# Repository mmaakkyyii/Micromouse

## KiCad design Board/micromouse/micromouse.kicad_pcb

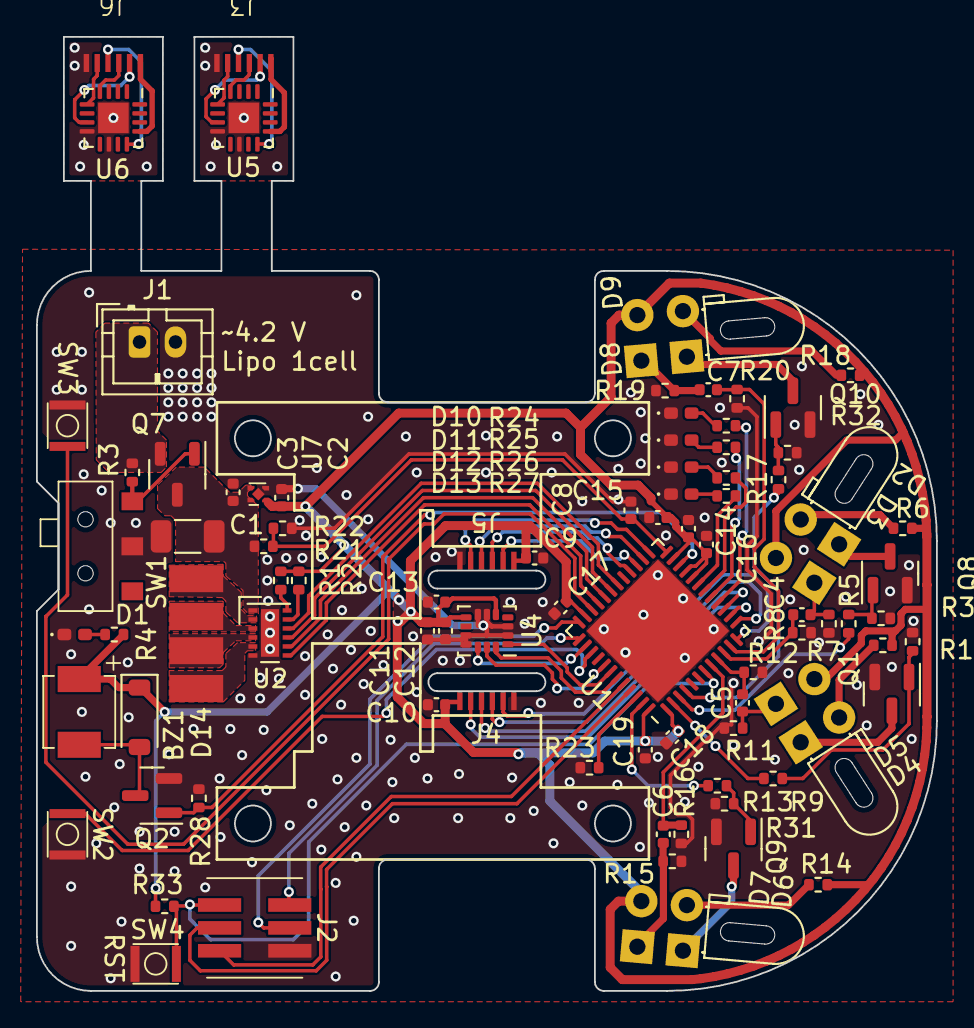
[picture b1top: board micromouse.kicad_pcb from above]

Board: 2 copper layers, 50.0 x 53.0 mm, 91 parts (0 on the bottom side), 83 nets.

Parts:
BZ1: SMT-0440-T-HT-R
C1: 10u; C_1206_3216Metric
C2, C3: 1u; C_0402_1005Metric
C4, C5, C6, C7: 0.01u; C_0402_1005Metric
C8, C9, C10, C12, C14, C15, C16, C17, C18, C19: 0.1u; C_0402_1005Metric
C11: 2.2u; C_0402_1005Metric
C13: 10n; C_0402_1005Metric
D1, D10, D11, D12, D13: LED; LED_0402_1005Metric_Pad0.77x0.64mm_HandSolder
D2, D4, D6, D8: OSI5FU3A11C; LED
D3, D5, D7, D9: LTR-4206E; PhotoDiode
D14: 1N4448W-TP; D_SOD-123
J1: Conn_01x02_Pin; JST_PH_B2B-PH-K_1x02_P2.00mm_Vertical
J2: Conn_02x03_Odd_Even; 20021221-00006C4LF
J3, J4, J5, J6: Conn_01x06_Pin; ENC_CONN
M1, M2: Motor_DC; Motor_PAD
Q1, Q2, Q8, Q9, Q10: DMN63D8L-7; SOT-23
Q7: GSFC02A05; SOT-23-3
R1, R2, R23: 0; R_0402_1005Metric
R3: 100k; R_0402_1005Metric
R4, R24, R25, R26, R27: 3.3k; R_0402_1005Metric
R5, R9, R13, R17: 10; R_0402_1005Metric
R6, R10, R14, R18: 15; R_0402_1005Metric
R7, R11, R15, R19: 300; R_0402_1005Metric
R8, R12, R16, R20, R28, R29, R30, R31, R32, R33: 10k; R_0402_1005Metric
R21: 6.8k; R_0402_1005Metric
R22: 15k; R_0402_1005Metric
SW1: AYZ0102AGRLC
SW2, SW3, SW4: NANOT 100 AS
U1: STM32G474CEUx; QFN-48-1EP_7x7mm_P0.5mm_EP5.6x5.6mm
U2: DRV8836DSSR; WSON-12-1EP_3x2mm_P0.5mm_EP1x2.65
U4: ICM-42688-P; LGA-14_3x2.5mm_P0.5mm_LayoutBorder3x4y
U5, U6: MAQ473GQE-AEC1-Z; QFN-16-1EP_3x3mm_P0.5mm_EP1.7x1.7mm
U7: NCP177AMX330TCG; XDFN4 1.0x1.0, 0.65P

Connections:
+3.3V: BZ1.1 (-), C2.1, C9.1, C10.1, C11.1, C12.1, C13.1, C14.1, C15.1, C16.1, C17.1, C18.1, C19.1, D3.2 (A), D5.2 (A), D7.2 (A), D9.2 (A), D14.1 (K), J4.1, J5.1, R1.2, R2.2, R4.1, R6.1, R10.1, R14.1, R18.1, R33.1, U1.1 (VBAT), U1.20 (VREF+), U1.21 (VDDA), U1.23 (VDD), U1.35 (VDD), U1.48 (VDD), U4.5 (VDDIO), U4.8 (VDD), U7.1 (OUT)
/AIN1: U1.30 (PA8), U2.10 (AIN1/APHASE)
/AIN2: U1.31 (PA9), U2.9 (AIN2/AENBL)
/BATT_ADC: C8.1, R21.2, R22.1, U1.24 (PB11)
/BIN1: U1.32 (PA10), U2.8 (BIN1/BPHASE)
/BIN2: U1.33 (PA11), U2.7 (BIN2/BENBL)
/BUZZER: Q2.1 (G), R28.2, U1.22 (PB10)
/ENC1/ENC_CS: J6.5, U6.5 (CS)
/ENC1/ENC_GND: J6.6, U6.8 (GND), U6.10 (TEST), U6.17 (EX_PAD)
/ENC1/ENC_MISO: J6.2, U6.7 (MISO)
/ENC1/ENC_MOSI: J6.3, U6.4 (MOSI)
/ENC1/ENC_SCLK: J6.4, U6.12 (SCLK)
/ENC1/ENC_VDD: J6.1, U6.13 (VDD)
/ENC/ENC_CS: J3.5, U5.5 (CS)
/ENC/ENC_GND: J3.6, U5.8 (GND), U5.10 (TEST), U5.17 (EX_PAD)
/ENC/ENC_MISO: J3.2, U5.7 (MISO)
/ENC/ENC_MOSI: J3.3, U5.4 (MOSI)
/ENC/ENC_SCLK: J3.4, U5.12 (SCLK)
/ENC/ENC_VDD: J3.1, U5.13 (VDD)
/LED1: R24.2, U1.16 (PC4)
/LED2: R25.2, U1.17 (PB0)
/LED3: R26.2, U1.18 (PB1)
/LED4: R27.2, U1.19 (PB2)
/LED_FL: R17.1, U1.4 (PC15)
/LED_FR: R13.1, U1.47 (PB9)
/LED_L: R5.1, U1.3 (PC14)
/LED_R: R9.1, U1.2 (PC13)
/NRST: J2.1, R33.2, SW4.2, U1.7 (PG10)
/SENSOR_FL: C7.2, R20.1, U1.11 (PA3)
/SENSOR_FR: C6.2, R16.1, U1.8 (PA0)
/SENSOR_L: C4.2, R8.1, U1.10 (PA2)
/SENSOR_R: C5.2, R12.1, U1.9 (PA1)
/SPI1_CLK: J4.4, U1.13 (PA5)
/SPI1_MISO: J4.2, U1.14 (PA6)
/SPI1_MOSI: J4.3, U1.15 (PA7)
/SPI1_NSS: J4.5, U1.12 (PA4)
/SPI2_CLK: J5.4, U1.26 (PB13)
/SPI2_MISO: J5.2, U1.27 (PB14)
/SPI2_MOSI: J5.3, U1.28 (PB15)
/SPI2_NSS: J5.5, U1.25 (PB12)
/SPI3_CLK: U1.41 (PB3), U4.13 (AP_SCLK/AP_SCLK)
/SPI3_MISO: U1.42 (PB4), U4.1 (AP_SDO/AP_AD0)
/SPI3_MOSI: U1.43 (PB5), U4.14 (AP_SDA/AP_SDIO/AP_SDI)
/SPI3_NSS: U1.38 (PA15), U4.12 (AP_CS)
/SW1: SW2.2, U1.39 (PC10)
/SW2: SW3.2, U1.34 (PA12)
/SYS_JTMS-SWCLK: J2.2, U1.37 (PA14)
/SYS_JTMS-SWDIO: J2.4, U1.36 (PA13)
/UART1_RX: J2.3, U1.45 (PB7)
/UART1_TX: J2.5, U1.44 (PB6)
GND: C1.2, C2.2, C3.2, C8.2, C9.2, C10.2, C11.2, C12.2, C13.2, C14.2, C15.2, C16.2, C17.2, C18.2, C19.2, D1.1 (K), D10.1 (K), D11.1 (K), D12.1 (K), D13.1 (K), J1.2, J2.6, J4.6, J5.6, Q1.2 (S), Q2.2 (S), Q8.2 (S), Q9.2 (S), Q10.2 (S), R7.2, R8.2, R11.2, R12.2, R15.2, R16.2, R19.2, R20.2, R22.2, R23.1, R28.1, R29.2, R30.2, R31.2, R32.2, SW1.2 (B), SW2.1, SW3.1, SW4.1, U1.49 (VSS), U2.6 (GND), U2.13 (EPAD), U4.2 (RESV), U4.3 (RESV), U4.6 (GND), U4.7 (RESV), U4.10 (RESV), U4.11 (RESV), U7.2 (GND)
unnamed: BZ1.2 (+), D14.2 (A), Q2.3 (D)
unnamed: D1.2 (A), R4.2
unnamed: D2.2 (A), R6.2
unnamed: D2.1 (K), Q8.3 (D)
unnamed: C4.1, D3.1 (K), R7.1
unnamed: D4.2 (A), R10.2
unnamed: D4.1 (K), Q1.3 (D)
unnamed: C5.1, D5.1 (K), R11.1
unnamed: D6.2 (A), R14.2
unnamed: D6.1 (K), Q9.3 (D)
unnamed: C6.1, D7.1 (K), R15.1
unnamed: D8.2 (A), R18.2
unnamed: D8.1 (K), Q10.3 (D)
unnamed: C7.1, D9.1 (K), R19.1
unnamed: D10.2 (A), R24.1
unnamed: D11.2 (A), R25.1
unnamed: D12.2 (A), R26.1
unnamed: D13.2 (A), R27.1
unnamed: J1.1, Q7.2 (S), R3.1
unnamed: M1.1 (+), U2.2 (AOUT1)
unnamed: M1.2 (-), U2.3 (AOUT2)
unnamed: M2.1 (+), U2.4 (BOUT1)
unnamed: M2.2 (-), U2.5 (BOUT2)
unnamed: Q1.1 (G), R9.2, R29.1
unnamed: Q7.1 (G), R3.2, SW1.1 (A)
unnamed: Q8.1 (G), R5.2, R30.1
unnamed: Q9.1 (G), R13.2, R31.1
unnamed: Q10.1 (G), R17.2, R32.1
unnamed: R23.2, U1.46 (PB8)
unnamed: R2.1, U2.11 (MODE)
unnamed: R1.1, U2.12 (nSLEEP)
VCC: C1.1, C3.1, Q7.3 (D), R21.1, U2.1 (VCC), U7.3 (EN), U7.4 (IN)

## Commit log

2023-06-23 add readme
2023-10-05 add kicad file
2023-10-11 レビュー対応
2023-10-11 余計なべたパターン削除
2023-10-12 ボタン位置修正
2023-10-16 部品型番、URLを追加
